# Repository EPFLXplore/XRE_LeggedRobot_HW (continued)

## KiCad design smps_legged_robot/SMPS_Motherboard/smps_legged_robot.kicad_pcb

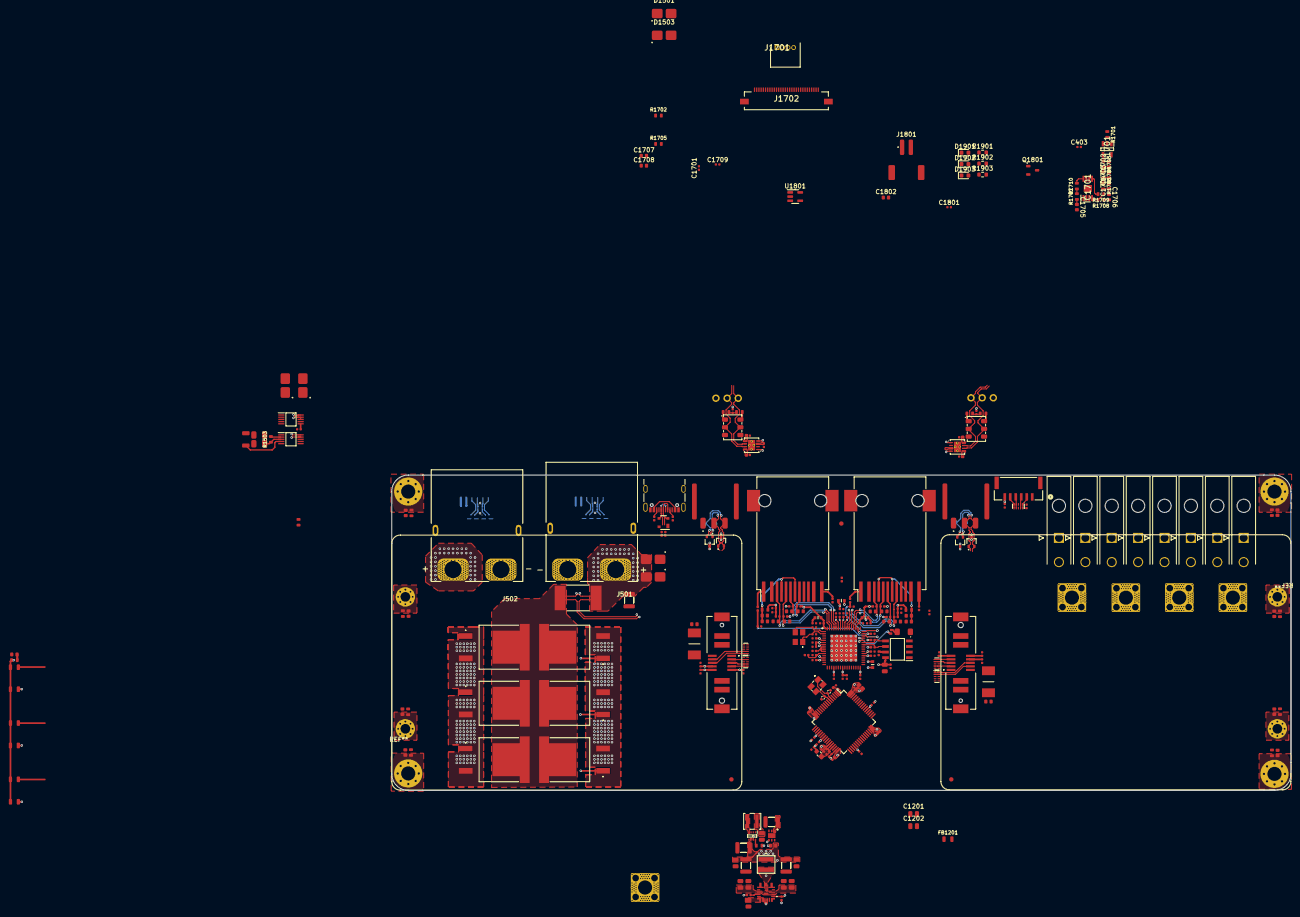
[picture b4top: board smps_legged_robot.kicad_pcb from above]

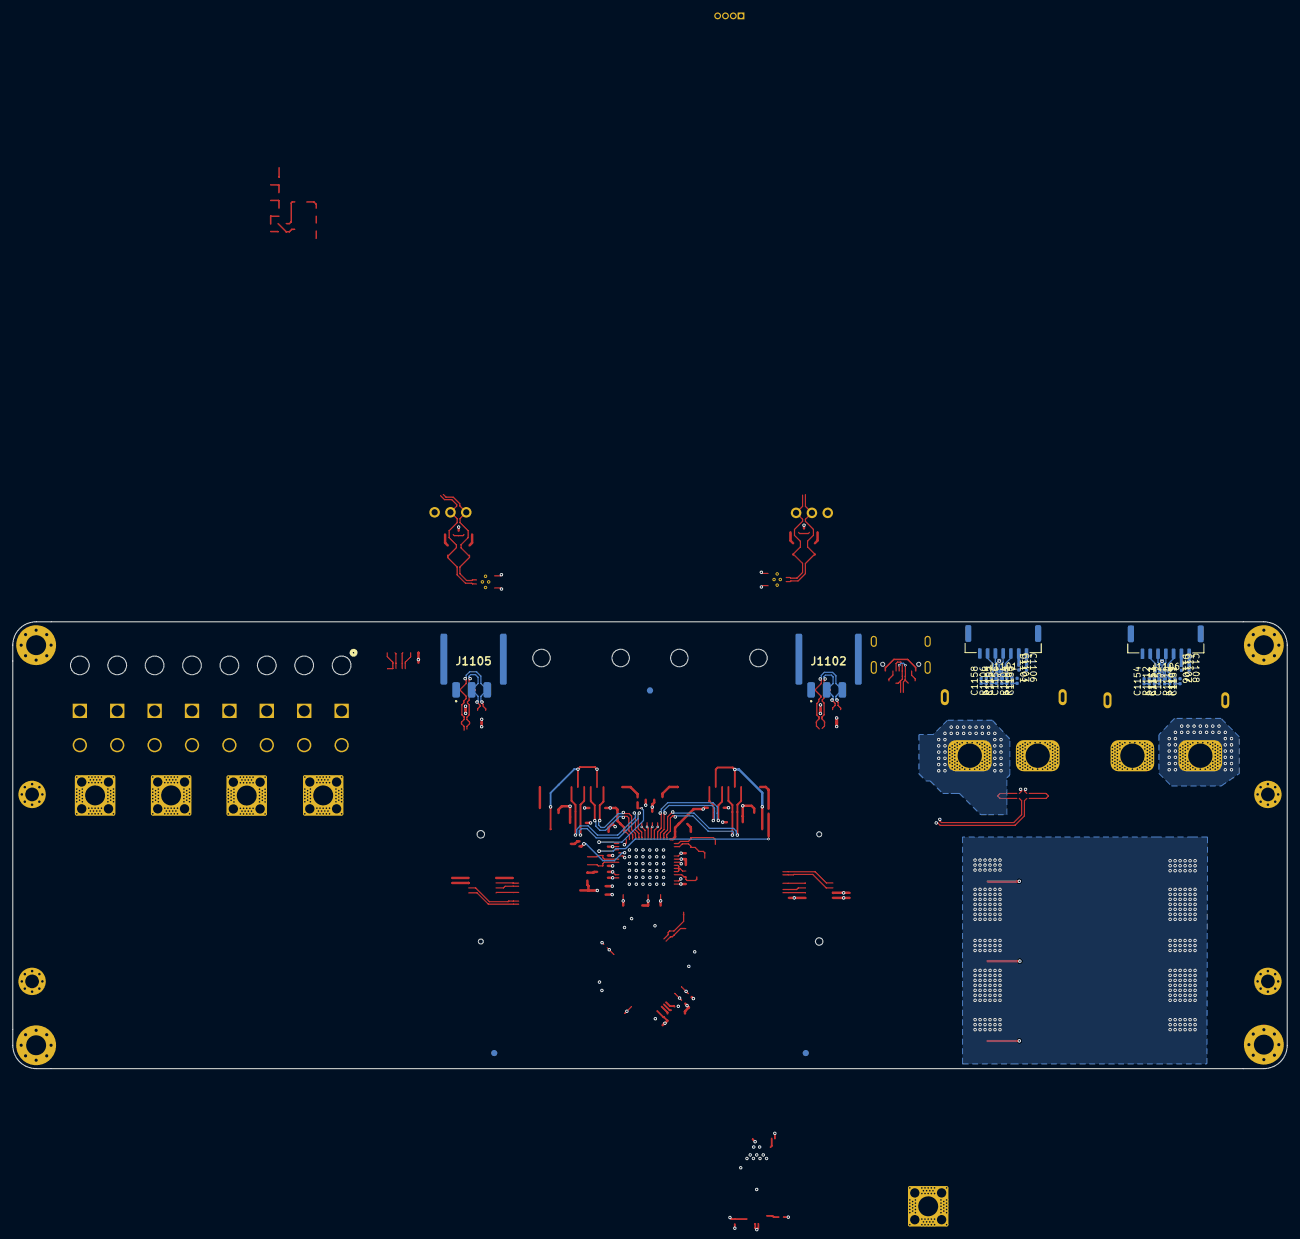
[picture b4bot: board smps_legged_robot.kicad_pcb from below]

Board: 6 copper layers, 204.5 x 71.7 mm, 308 parts (29 on the bottom side), 153 nets.

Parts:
C401, C402: 12p NP0 25V; C_0402_1005Metric
C403, C404, C405, C407, C408, C409, C410, C414, C416, C1101, C1102, C1103, C1104, C1105, C1106, C1107, C1108, C1109, C1110, C1112, C1113, C1115, C1116, C1117, C1118, C1119, C1120, C1121, C1122, C1123, C1124, C1125, C1126, C1127, C1128, C1139, C1140, C1145, C1146, C1147, C1206, C1301, C1303, C1305, C1701, C1709, C1801, C2001, C2501, C2503, C2505: 100n X7R 50V; C_0402_1005_DensityHigh
C406, C412, C413, C415: 1u X7R 10V; C_0402_1005_DensityHigh
C411: 4u7 X7R 16V; C_0603_1608_DensityHigh
C801, C1201, C1202, C1203: 2u2 X7R 100V; C_0805_2012_DensityHigh
C802, C1204: 100n X7R 100V; C_0805_2012_DensityHigh
C803, C1207: 10u X7R 25V; C_1210_3225_DensityHigh
C804, C805, C1148, C1205: 2.2u X7R 25V; C_0805_2012_DensityHigh
C1111: 1u X7R 50V; C_0402_1005_DensityHigh
C1114: 220p X7R 50V; C_0402_1005_DensityHigh
C1129, C1130, C1131, C1132, C1134, C1135, C1137, C1138: 15p X7R 50V; C_0603_1608_DensityHigh
C1133, C1136: 18p NP0 50V; C_0402_1005_DensityHigh
C1141, C1142, C1143, C1144: 22n X7R 50V; C_0603_1608_DensityHigh
C1149, C1150: 4n7 X7R 100V; C_0402_1005_DensityHigh
C1151, C1152, C1153, C1154, C1155, C1156, C1157, C1158: DNP; C_0402_1005_DensityHigh
C1208: 4.7uF X7R 25V; C_1210_3225_DensityHigh
C1209: 1u X7R 25V; C_0603_1608_DensityHigh
C1210: 22u X7R 10V; C_1210_3225_DensityHigh
C1211: 22u X7R 10V; C_0805_2012_DensityHigh
C1302, C1401: 100n X7R 100V; C_0603_1608_DensityHigh
C1501: 10uF X7R 100V; C_1210_3225_DensityHigh
C1502: 2nF X7R 50V; C_1206_3216_DensityHigh
C1503: 110n X7R 100V; C_0603_1608_DensityHigh
C1702, C1703, C1704: 4.7n X7R 50V; C_0603_1608_DensityHigh
C1705, C1706: 470n X5R 16V; C_0603_1608_DensityHigh
C1707: 220n X7R 10V; C_0603_1608_DensityHigh
C1708: 1u X7R 16V; C_0603_1608_DensityHigh
C1802: 4.7u X7R 16V; C_0603_1608_DensityHigh
C2102, C2103, C2104, C2105, C2201, C2202, C2203, C2204: 1n X7R 1kV; C_0603_1608_DensityHigh
D401: PRTR5V0U2X; SOT-143
D402: PESD4USB3U-TBSX; SOT1176D
D501, D502, D503, D504, D1501, D1503: SMBJ51CD-M3/H; DIOM4336X24N
D1101, D1106, D1301, D1302, D1401, D2501: PESD4USB5B-TBSX; SOT1176D
D1102, D1103, D1104, D1105: PESD2CANFD24V-UX; SOT95P230X117-3N
D1107: ORANGE; LED_SM1206
D1901: YELLOW; LED_0603_1608Metric
D1902: GREEN; LED_0603_1608Metric
D1903: USB; LED_0603_1608Metric
F1301, F1401: 0451015.MRL; FUSC6127X294N
FB401: 100R@100MHz; L_0603_1608Metric
FB1101, FB1102, FB1103, FB1104: BLM18PG330SN1D; BLM18SP221SN1B
FB1201: 1k @ 100MHz; R_0805_2012_DensityHigh
FM2201, FM2202, FM2203, FM2204, FM2205, FM2206: Fiducial; Fiducial_1mm_Mask2mm
H2101, H2102, H2103, H2104: M2 (3.2mm); MountingHole_2.2mm_M2_Pad_Via
H2201, H2202, H2203, H2204: M3 (3.2mm); MountingHole_3.2mm_M3_Pad_Via
IC1101: LAN9252_ML; QFN50P900X900X100-65N-D
IC1102: M24C16-RMN6P; SOIC127P600X175-8N
IC1201: MAX25262AFOF_VY+; MAX25262AFOFVY
IC1202: TPS629206QDRLRQ1; SOTFL50P160X60-8N
IC1203: TPS7A2650DRVR; SON65P200X200X80-7N
IC1501: TPS2490DGSRG4; SOP50P490X110-10N
IC1701: TPA6205A1DGN; SOP65P490X110-9N
IC2001: INA239AQDGSRQ1; SOP50P490X110-10N
J301: Rail 1; Pad_Square_Vias_6.5x6.5mm
J302: Rail 2; Pad_Square_Vias_6.5x6.5mm
J303: Rail 3; Pad_Square_Vias_6.5x6.5mm
J304: Rail 4; Pad_Square_Vias_6.5x6.5mm
J305: Vin; Pad_Square_Vias_6.5x6.5mm
J402: Conn_Picoblade_JST_DEBUG; CONN_SM06B-GHS-TB_JST
J403: USB4105-GF-A; USB_C_Receptacle_GCT_USB4105-xx-A_16P_TopMnt_Horizontal
J501: XT90PW-M; AMASS_XT90PW-M
J502: XT90PW-F; AMASS_XT90PW-F
J1101, J1106: SM07B-GHS-TB; JST_GH_SM07B-GHS-TB_1x07-1MP_P1.25mm_Horizontal
J1102, J1103, J1104, J1105: Nano-Fit 1x03; 1054301203
J1107, J1108: RJ45_Wuerth_74980111211; RJ45_Wuerth_74980111211_Horizontal
J1109, J1110: PTH 01x03 2.54mm; PTH_1x03_P2.54mm
J1301, J2501: 10159558-410421RLF; 10159558410421RLF
J1701: 53048-0450; SHDRRA4W35P0X125_1X4_675X550X350P
J1702: 505110-3091; 5051103091
J1801: Screw_Terminal_01x02; JST_PH_S2B-PH-SM4-TB_1x02-1MP_P2.00mm_Horizontal
L801: 3.3uH; XEL4030682MEC
L1202: 2.2uH; IND_XGL3530_COC
Molex_601, Molex_602, Molex_603, Molex_604, Molex_605, Molex_606, Molex_607, Molex_608: 172448-YY02
NT1101, NT1601: NetTieShuntH; NetTie-2_SMD_Pad0.2mm
NT1103, NT1602: NetTieShuntL; NetTie-2_SMD_Pad0.2mm
Q1601, Q1602, Q1603, Q1604, Q1605, Q1606: PSMN4R8-100BSEJ; PHB45NQ15T118
Q1801: PMV90ENER; SOT-23-3
R401: 33k 1% 1/16W; R_0402_1005_DensityHigh
R402, R403: 5.1k 1% 1/16W; R_0402_1005_DensityHigh
R404, R405, R406, R1101, R1102, R1201: 10k 1% 1/16W; R_0402_1005_DensityHigh
R407, R408: 27R 1% 1/5W; R_0402_1005_DensityHigh
R1103, R1104, R1105, R1106, R1109, R1110, R1111, R1112: 100R 1% 1/5W; R_0402_1005_DensityHigh
R1107, R1108, R1138, R1139: 60R4 1% 1/4W; R_0603_1608_DensityHigh
R1113, R1114, R1115, R1128, R1129, R1130, R1135, R1136: 4.75k 0.1% 1/16W; R_0402_1005_DensityHigh
R1116: 12k 1%, 1/16W; R_0402_1005_DensityHigh
R1117, R1118, R1119, R1120, R1121, R1122, R1123, R1124: 49.9R 0.1% 1/16W; R_0402_1005_DensityHigh
R1125, R1131, R1132, R1133, R1134: 470R 1% 1/16W; R_0402_1005_DensityHigh
R1126, R1127: 10R 1% 1/8W; R_0603_1608_DensityHigh
R1202: 34k 1% 1/4W; R_0603_1608_DensityHigh
R1501: 212k 1% 1/10W; R_0603_1608_DensityHigh
R1502: 10k 1% 1/4W; R_1206_3216_DensityHigh_Large
R1503: 45k 1% 1/10W; R_0603_1608_DensityHigh
R1504: 7,5k 1% 1/4W; R_1206_3216_DensityHigh_Large
R1505: 0.3m; RES_WSLP3921_.003OHM_VIS
R1507, R1703, R1704, R1706: 1k 1% 1/10W; R_0603_1608_DensityHigh
R1601, R1602, R1603, R1604, R1605, R1606: 10R 1% 1/8W; R_0805_2012_DensityHigh
R1701, R1702: 33 1% 1/10W; R_0603_1608_DensityHigh
R1705: 47k 1% 1/10W; R_0603_1608_DensityHigh
R1707, R1708: 10k 1% 1/10W; R_0603_1608_DensityHigh
R1709, R1710: 20k 1% 1/10W; R_0603_1608_DensityHigh
R1901: 768R 1% 1/8W; R_0603_1608Metric
R1902, R1903: 40R 5% 1/4W; R_0603_1608Metric
R2102, R2103, R2104, R2105, R2201, R2202, R2203, R2204: 0R; R_0603_1608_DensityHigh
SW1101, SW1103: CAS-220TA; CAS-220A_NDC-L
U401: STM32G483RET6; LQFP-64_10x10mm_P0.5mm
U1101, U1102: TCAN1051HGVDRBRQ1; HVSON-8-1EP_3x3mm_P0.65mm_EP1.6x2.4mm_ThermalVias
U1701: 74LVC1G125; SOT95P280X145-5N
U1801: DGD0216WT-7; TSOT-23-5
Y401: ABM8W-48.0000MHZ-4-D1X-T3; ABM8W480000MHZ6D1XT3
Y1101: 7M-25.000MAAJ-T; 7M25000MAAJT

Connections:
+3.3VA: C413.1, C414.1, C415.1, C416.1, FB401.1, U401.28 (VREF+), U401.29 (VDDA)
+3V3: C403.1, C404.1, C406.1, C407.1, C408.1, C409.1, C410.1, C411.1, C412.1, C1101.1, C1102.1, C1106.1, C1108.1, C1109.1, C1110.1, C1116.1, C1117.1, C1118.1, C1119.1, C1121.1, C1123.1, C1128.1, C1147.1, C1148.1, C1211.1, C1301.1, C1701.1, C1708.1, C2001.1, C2501.1, D401.4 (VCC), FB401.2, FB1101.1, FB1102.1, FB1103.1, IC1101.5 (VDD33), IC1101.7 (REG_EN), IC1101.14 (VDDIO), IC1101.20 (VDDIO), IC1101.32 (VDDIO), IC1101.37 (VDDIO), IC1101.47 (VDDIO), IC1102.8 (VCC), IC1202.3 (VOS), IC1701.6 (VDD), IC2001.6 (VS), J402.6, J1101.1, J1106.1, J1301.S10, J2501.S10, L1202.2, R401.2, R404.2, R405.2, R406.2, R1113.2, R1114.2, R1128.2, R1129.2, R1901.2, R1902.2, R1903.2, U401.1 (VBAT), U401.16 (VDD), U401.32 (VDD), U401.48 (VDD), U401.64 (VDD), U1101.5 (VIO), U1102.5 (VIO), U1701.5 (VCC)
+3V3_A: C1126.1, C1140.1, C1146.1, FB1102.2, IC1101.51 (VDD33TXRX1), R1117.1, R1119.1, R1121.1, R1123.1, R1126.1
+3V3_B: C1127.1, C1139.1, C1145.1, FB1103.2, IC1101.64 (VDD33TXRX2), R1118.1, R1120.1, R1122.1, R1124.1, R1127.1
+5V: C1103.1, C1104.1, C1105.1, C1107.1, C1210.1, C1303.1, C1709.1, C1801.1, C1802.1, C2503.1, IC1203.1 (OUT), J1101.2, J1106.2, J1301.S9, J1702.26, J1702.27, J2501.S9, U1101.3 (VCC), U1102.3 (VCC), U1801.5 (VCC)
+12V: C803.2, C804.2, C805.2, C1207.2, C1208.2, C1209.2, C1305.1, C2505.1, IC1201.14 (EXTVCC), IC1201.15 (OUT), IC1202.6 (VIN), IC1203.6 (IN), J1301.S8, J1801.1, J2501.S8, L801.2, R1201.2
+VBAT: C1501.1, D501.2 (A2), D502.2 (A2), D1501.2 (A2), D1503.2 (A2), J501.2, NT1101.2, R1501.2, R1505.1
+VIN: C1201.1, D503.2 (A2), D504.2 (A2), F1301.1, F1401.1, FB1201.1, IC1501.7 (OUT), J305.1, Q1601.3 (S), Q1602.3 (S), Q1603.3 (S), Q1604.3 (S), Q1605.3 (S), Q1606.3 (S)
/Project Architecture/Connectors - Communication/EXT_A_PIN1: C1155.1, R1103.1
/Project Architecture/Connectors - Communication/EXT_A_PIN2: C1156.1, R1104.1
/Project Architecture/Connectors - Communication/EXT_A_PIN3: C1157.1, R1105.1
/Project Architecture/Connectors - Communication/EXT_A_PIN4: C1158.1, R1106.1
/Project Architecture/Connectors - Communication/EXT_B_PIN1: C1151.1, R1109.1
/Project Architecture/Connectors - Communication/EXT_B_PIN2: C1152.1, R1110.1
/Project Architecture/Connectors - Communication/EXT_B_PIN3: C1153.1, R1111.1
/Project Architecture/Connectors - Communication/EXT_B_PIN4: C1154.1, R1112.1
/Project Architecture/Connectors - Communication/FDCAN1_N: D1102.2 (K2), D1103.2 (K2), J1104.3, J1105.3, J1110.2, SW1101.5 (B), U1102.6 (CANL)
/Project Architecture/Connectors - Communication/FDCAN1_P: D1102.1 (K1), D1103.1 (K1), J1104.2, J1105.2, J1110.3, SW1101.2 (B), U1102.7 (CANH)
/Project Architecture/Connectors - Communication/FDCAN1_S: R1102.1, U1102.8 (S)
/Project Architecture/Connectors - Communication/FDCAN2_N: D1104.2 (K2), D1105.2 (K2), J1102.3, J1103.3, J1109.3, SW1103.5 (B), U1101.6 (CANL)
/Project Architecture/Connectors - Communication/FDCAN2_P: D1104.1 (K1), D1105.1 (K1), J1102.2, J1103.2, J1109.2, SW1103.2 (B), U1101.7 (CANH)
/Project Architecture/Connectors - Communication/FDCAN2_S: R1101.1, U1101.8 (S)
/Project Architecture/Connectors - Communication/IRQ: IC1101.44 (IRQ), R1114.1
/Project Architecture/Connectors - Communication/LED_ON1: IC1101.48 (LINKACTLED0/TDO/~CHIP_MODE0), R1132.2, R1135.2
/Project Architecture/Connectors - Communication/LED_ON2: IC1101.46 (LINKACTLED1/TDI/~CHIP_MODE1), R1134.2, R1136.2
/Project Architecture/Connectors - Communication/RXA_N: C1137.1, IC1101.54 (RXNA), J1107.8 (RD-), R1123.2
/Project Architecture/Connectors - Communication/RXA_P: C1134.1, IC1101.55 (RXPA), J1107.6 (RD+), R1121.2
/Project Architecture/Connectors - Communication/RXB_N: C1138.1, IC1101.61 (RXNB), J1108.8 (RD-), R1124.2
/Project Architecture/Connectors - Communication/RXB_P: C1135.1, IC1101.60 (RXPB), J1108.6 (RD+), R1122.2
/Project Architecture/Connectors - Communication/TXA_N: C1131.1, IC1101.52 (TXNA), J1107.5 (TD-), R1119.2
/Project Architecture/Connectors - Communication/TXA_P: C1129.1, IC1101.53 (TXPA), J1107.3 (TD+), R1117.2
/Project Architecture/Connectors - Communication/TXB_N: C1132.1, IC1101.63 (TXNB), J1108.5 (TD-), R1120.2
/Project Architecture/Connectors - Communication/TXB_P: C1130.1, IC1101.62 (TXPB), J1108.3 (TD+), R1118.2
/Project Architecture/Connectors - Rail Out 1/RAIL1: J301.1, Molex_601.1 (Vout), Molex_602.1 (Vout)
/Project Architecture/Connectors - Rail Out 1/RAIL2: J302.1, Molex_603.1 (Vout), Molex_604.1 (Vout)
/Project Architecture/Connectors - Rail Out 1/RAIL3: J303.1, Molex_605.1 (Vout), Molex_606.1 (Vout)
/Project Architecture/Connectors - Rail Out 1/RAIL4: J304.1, Molex_607.1 (Vout), Molex_608.1 (Vout)
/Project Architecture/Interface - Display/APWM: J1702.10, R1701.1
/Project Architecture/Interface - Display/nSHDN: J1702.12, R1702.1
/Project Architecture/Interface - FAN /FAN: U401.55 (PD2), U1801.3 (IN)
/Project Architecture/MCU - Unit/JTCK-SWCLK: D402.4 (K), D402.7 (K), J402.4, U401.50 (PA14)
/Project Architecture/MCU - Unit/JTMS-SWDIO: D402.5 (K), D402.6 (K), J402.5, U401.49 (PA13)
/Project Architecture/MCU - Unit/JTMS-SWO: D402.2 (K), D402.9 (K), J402.3, U401.56 (PB3)
/Project Architecture/MCU - Unit/LED_USB: J403.A4 (VBUS), J403.A9 (VBUS), J403.B4 (VBUS), J403.B9 (VBUS)
/Project Architecture/MCU - Unit/NRST: C405.1, D402.1 (K), D402.10 (K), J402.2, U401.7 (PG10)
/Project Architecture/MCU - Unit/PROG_CHARGE: IC1501.6 (PG), R401.1, U401.23 (PC5)
/Project Architecture/MCU - Unit/SPI1_MISO: R405.1, U401.20 (PA6)
/Project Architecture/MCU - Unit/SPI2_MISO: R406.1, U401.36 (PB14)
/Project Architecture/MCU - Unit/SPI3_MISO: R404.1, U401.53 (PC11)
/Project Architecture/MCU - Unit/USB+: R407.2, U401.45 (PA11)
/Project Architecture/MCU - Unit/USB-: R408.2, U401.46 (PA12)
/Project Architecture/MCU - Unit/USB_C+: D401.2 (I/O1), J403.A7 (D-), J403.B7 (D-), R407.1
/Project Architecture/MCU - Unit/USB_C-: D401.3 (I/O2), J403.A6 (D+), J403.B6 (D+), R408.1
/Project Architecture/Power - Local Generation/12V_Good: IC1201.1 (PGOOD), IC1202.7 (EN), IC1203.4 (EN), R1201.1
/Project Architecture/Power - Module A/ALERT: D1301.5 (K), D1301.6 (K), J1301.S7
/Project Architecture/Power - Module A/RUN0: D1301.4 (K), D1301.7 (K), J1301.S5
/Project Architecture/Power - Module A/RUN1: D1302.1 (K), D1302.10 (K), J1301.S6
/Project Architecture/Power - Module A/SCL: D1302.2 (K), D1302.9 (K), J1301.S4
/Project Architecture/Power - Module A/SDA: D1301.2 (K), D1301.9 (K), J1301.S3
/Project Architecture/Power - Module B/ALERT: D2501.5 (K), D2501.6 (K), J2501.S7
/Project Architecture/Power - Module B/RUN0: D2501.4 (K), D2501.7 (K), J2501.S5
/Project Architecture/Power - Module B/RUN1: D1401.1 (K), D1401.10 (K), J2501.S6
/Project Architecture/Power - Module B/SCL: D1401.2 (K), D1401.9 (K), J2501.S4
/Project Architecture/Power - Module B/SDA: D2501.2 (K), D2501.9 (K), J2501.S3
/Project Architecture/Power - Precharge/Power - MOS/G: IC1501.8 (GATE), R1507.1, R1601.1, R1602.2, R1603.1, R1604.2, R1605.1, R1606.2
/Project Architecture/Power - Precharge/TIMER: C1502.1, IC1501.4 (TIMER)
/Project Architecture/Power - Precharge/Vsense_low: NT1103.1, NT1602.2, Q1601.2 (D), Q1601.4 (D_2), Q1602.2 (D), Q1602.4 (D_2), Q1603.2 (D), Q1603.4 (D_2), Q1604.2 (D), Q1604.4 (D_2), Q1605.2 (D), Q1605.4 (D_2), Q1606.2 (D), Q1606.4 (D_2), R1505.2
/Project Architecture/Power - Precharge/shunt+: IC1501.10 (VCC), NT1101.1
/Project Architecture/Power - Precharge/shunt-: IC1501.9 (SENSE), NT1103.2
/Project Architecture/Sensor - Battery/shunt+: IC2001.10 (IN+), NT1601.1
/Project Architecture/Sensor - Battery/shunt-: IC2001.8 (VBUS), IC2001.9 (IN-), NT1602.1
GND: C401.2, C402.2, C403.2, C404.2, C405.2, C406.2, C407.2, C408.2, C409.2, C410.2, C411.2, C412.2, C413.2, C414.2, C415.2, C416.2, C801.2, C802.2, C803.1, C804.1, C805.1, C1101.2, C1102.2, C1103.2, C1104.2, C1105.2, C1106.2, C1107.2, C1108.2, C1109.2, C1110.2, C1111.2, C1112.1, C1113.2, C1114.2, C1115.1, C1116.2, C1117.2, C1118.2, C1119.2, C1120.2, C1121.2, C1122.2, C1123.2, C1124.2, C1125.2, C1126.2, C1127.2, C1128.2, C1129.2, C1130.2, C1131.2, C1132.2, C1133.2, C1134.2, C1135.2, C1136.2, C1137.2, C1138.2, C1139.2, C1140.2, C1141.2, C1142.2, C1143.2, C1144.2, C1145.2, C1146.2, C1147.2, C1148.2, C1149.2, C1150.2, C1151.2, C1152.2, C1153.2, C1154.2, C1155.2, C1156.2, C1157.2, C1158.2, C1201.2, C1202.2, C1203.2, C1204.2, C1205.2, C1207.1, C1208.1, C1209.1, C1210.2, C1211.2, C1301.2, C1302.2, C1303.2, C1305.2, C1401.2, C1501.2, C1502.2, C1503.2, C1701.2, C1702.2, C1703.2, C1704.2, C1705.2, C1707.2, C1708.2, C1709.2, C1801.2, C1802.2, C2001.2, C2102.2, C2103.2, C2104.2, C2105.2, C2201.2, C2202.2, C2203.2, C2204.2, C2501.2, C2503.2, C2505.2, D401.1 (GND), D402.3 (A), D402.8 (A), D501.1 (A1), D502.1 (A1), D503.1 (A1), D504.1 (A1), D1101.3 (A), D1101.8 (A), D1102.3 (CC), D1103.3 (CC), D1104.3 (CC), D1105.3 (CC), D1106.3 (A), D1106.8 (A), D1107.1 (K), D1301.3 (A), D1301.8 (A), D1302.3 (A), D1302.8 (A), D1401.3 (A), D1401.8 (A), D1501.1 (A1), D1503.1 (A1), D2501.3 (A), D2501.8 (A), IC1101.4 (OSCVSS), IC1101.41 (TESTMODE), IC1101.65 (VSS), IC1102.1 (NC_1), IC1102.2 (NC_2), IC1102.3 (NC_3), IC1102.4 (VSS), IC1201.5 (GND), IC1201.7 (PGND_2), IC1201.11 (GND), IC1201.16 (SYNC), IC1201.17 (SPS), IC1201.18 (SPS_2), IC1201.19 (PGND_3), IC1201.21 (PGND_4), IC1202.5 (GND), IC1203.2 (NC), IC1203.5 (GND), IC1203.7 (EP), IC1501.5 (GND), IC1701.7 (GND), IC1701.9 (EP), IC2001.7 (GND), J402.1, J403.A1 (GND), J403.A12 (GND), J403.B1 (GND), J403.B12 (GND), J403.S1 (SHIELD), J501.1, J1101.7, J1102.1, J1103.1, J1104.1, J1105.1, J1106.7, J1107.2, J1107.10, J1107.11, J1107.SH, J1108.2, J1108.10, J1108.11, J1108.SH, J1109.1, J1110.1, J1301.P2, J1702.1, J1702.5, J1702.9, J1702.11, J1702.13, J1702.17, J1702.21, J1702.24, J1702.25, J1702.30, J2501.P2, Molex_601.2 (GND), Molex_602.2 (GND), Molex_603.2 (GND), Molex_604.2 (GND), Molex_605.2 (GND), Molex_606.2 (GND), Molex_607.2 (GND), Molex_608.2 (GND), Q1801.3 (S), R402.1, R403.2, R1101.2, R1102.2, R1115.1, R1116.1, R1130.1, R1135.1, R1136.1, R1202.2, R1502.1, R1504.1, R1705.1, R2102.2, R2103.2, R2104.2, R2105.2, R2201.2, R2202.2, R2203.2, R2204.2, U401.15 (VSS), U401.27 (VSSA), U401.31 (VSS), U401.47 (VSS), U401.63 (VSS), U1101.2 (GND), U1101.9 (PAD), U1102.2 (GND), U1102.9 (PAD), U1701.1, U1701.3 (GND), U1801.2 (COM), Y401.2 (GND), Y401.4 (GND), Y1101.2
unnamed: C1111.1, C1114.1, C1120.1, C1122.1, C1124.1, FB1104.2, IC1101.6 (VDDCR), IC1101.24 (VDDCR), IC1101.38 (VDDCR)
unnamed: C1149.1, R1107.2, R1108.1
unnamed: C1150.1, R1138.2, R1139.1
unnamed: C1302.1, F1301.2, J1301.P1
unnamed: C1401.1, F1401.2, J2501.P1
unnamed: C1503.1, R1507.2
unnamed: C1702.1, R1703.2, R1704.1
unnamed: C1703.1, R1704.2, R1706.1
unnamed: C1704.1, C1706.1, R1706.2
unnamed: C1705.1, R1707.1
unnamed: C1706.2, R1708.1
unnamed: C2102.1, H2101.1, R2102.1
unnamed: C2103.1, H2104.1, R2103.1
unnamed: C2104.1, H2102.1, R2104.1
unnamed: C2105.1, H2103.1, R2105.1
unnamed: C2201.1, H2201.1, R2201.1
unnamed: C2202.1, H2202.1, R2202.1
unnamed: C2203.1, H2203.1, R2203.1
unnamed: C2204.1, H2204.1, R2204.1
unnamed: D1107.2 (A), R1125.1
unnamed: D1901.2 (A), R1901.1
unnamed: D1902.2 (A), R1902.1
unnamed: D1903.2 (A), R1903.1
unnamed: IC1101.43 (EESCL/TCK), IC1102.5 (SDA), R1128.1
unnamed: IC1101.42 (EESDA/TMS), IC1102.6 (SCL), R1129.1
unnamed: IC1101.8 (~FXLOSEN), IC1101.9 (FXSDA/FXLOSA/~FXSDENA), IC1101.10 (FXSDB/FXLOSB/~FXSDENB), R1115.2
unnamed: C1136.1, IC1101.1 (OSCI), Y1101.3
unnamed: C1133.1, IC1101.2 (OSCO), Y1101.1
unnamed: IC1101.57 (RBIAS), R1116.2
unnamed: C1113.1, IC1101.11 (RST#), R1113.1
unnamed: IC1101.45 (RUNLED/~E2PSIZE), R1125.2
unnamed: C1112.2, C1115.2, FB1104.1, IC1101.56 (VDD12TX1), IC1101.59 (VDD12TX2)
unnamed: C1125.1, FB1101.2, IC1101.58 (VDD33BIAS)
unnamed: IC1102.7 (~WC), R1130.2
unnamed: C1205.1, IC1201.12 (BIAS), IC1201.13 (FB), IC1201.22 (BIAS_2)
unnamed: C1206.1, IC1201.10 (BST)
unnamed: C801.1, C802.1, C1202.1, C1203.1, C1204.1, FB1201.2, IC1201.2 (EN), IC1201.3 (SUP), IC1201.9 (SUP_2), IC1201.23 (EP)
unnamed: C1206.2, IC1201.6 (LX), IC1201.20 (LX_2), L801.1
unnamed: IC1202.8 (MODE/S-CONF), R1202.1
unnamed: IC1202.4 (SW), L1202.1
unnamed: IC1501.1 (EN), R1501.1, R1502.2
unnamed: IC1501.3 (PROG), R1503.1, R1504.2
unnamed: IC1501.2 (VREF), R1503.2
unnamed: C1707.1, IC1701.2 (BYPASS)
unnamed: IC1701.3 (IN+), R1707.2, R1710.1
unnamed: IC1701.4 (IN-), R1708.2, R1709.1
unnamed: IC1701.5 (VO+), J1701.1, J1701.2, R1709.2
unnamed: IC1701.8 (VO-), J1701.3, J1701.4, R1710.2
unnamed: IC1701.1 (~SHUTDOWN), R1702.2, R1705.2
unnamed: J403.A5 (CC1), R402.2
unnamed: J403.B5 (CC2), R403.1
unnamed: D1101.1 (K), D1101.10 (K), J1101.3, R1103.2
unnamed: D1101.2 (K), D1101.9 (K), J1101.4, R1104.2
unnamed: D1101.4 (K), D1101.7 (K), J1101.5, R1105.2
unnamed: D1101.5 (K), D1101.6 (K), J1101.6, R1106.2
unnamed: D1106.1 (K), D1106.10 (K), J1106.3, R1109.2
unnamed: D1106.2 (K), D1106.9 (K), J1106.4, R1110.2
unnamed: D1106.4 (K), D1106.7 (K), J1106.5, R1111.2
unnamed: D1106.5 (K), D1106.6 (K), J1106.6, R1112.2
unnamed: J1107.1, R1132.1
unnamed: J1107.12, R1131.1
unnamed: C1141.1, C1143.1, J1107.4 (TCT), J1107.7 (RCT), R1126.2
unnamed: J1108.1, R1134.1
unnamed: J1108.12, R1133.1
unnamed: C1142.1, C1144.1, J1108.4 (TCT), J1108.7 (RCT), R1127.2
unnamed: J1801.2, Q1801.1 (D)
unnamed: Q1601.1 (G), R1601.2
unnamed: Q1602.1 (G), R1602.1
unnamed: Q1603.1 (G), R1603.2
unnamed: Q1604.1 (G), R1604.1
unnamed: Q1605.1 (G), R1605.2
unnamed: Q1606.1 (G), R1606.1
unnamed: Q1801.2 (G), U1801.4 (OUT)
unnamed: R1701.2, U1701.2
unnamed: R1703.1, U1701.4
unnamed: R1107.1, SW1101.1 (A)
unnamed: R1108.2, SW1101.4 (A)
unnamed: R1138.1, SW1103.1 (A)
unnamed: R1139.2, SW1103.4 (A)
unnamed: C401.1, U401.5 (PF0), Y401.1 (IN)
unnamed: C402.1, U401.6 (PF1), Y401.3 (OUT)
